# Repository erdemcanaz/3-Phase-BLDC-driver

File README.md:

# 3-Phase-BLDC-driver
A storyline of designing ~400Watt sensored brushless DC motor driver.

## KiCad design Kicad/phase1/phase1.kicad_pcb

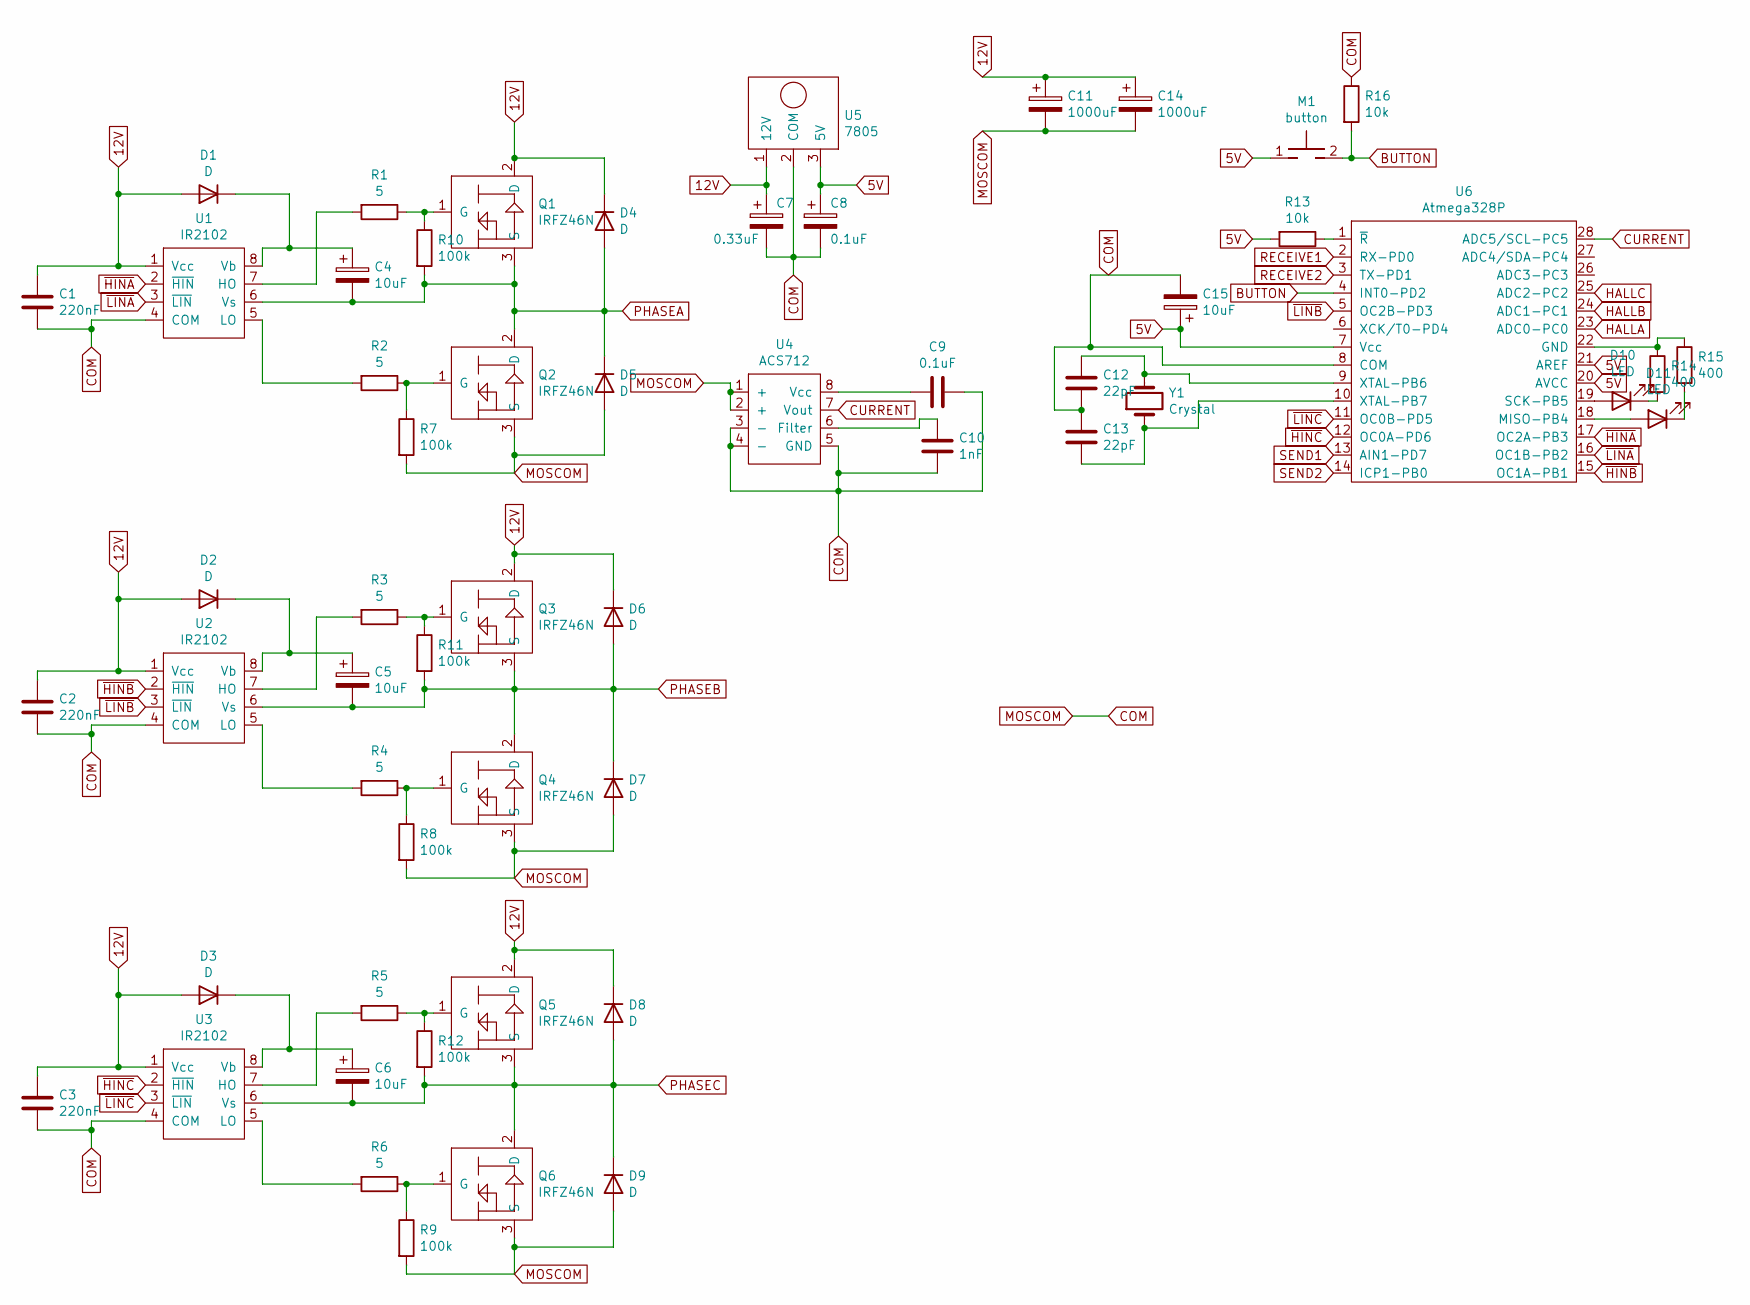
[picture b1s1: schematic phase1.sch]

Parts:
C1, C2, C3: 220nF; 3mm- circle
C4, C5, C6, C15: 10uF; SMD-1210
C7: 0.33uF; 3mm- circle
C8, C9: 0.1uF; 3mm- circle
C10: 1nF; 3mm- circle
C11, C14: 1000uF; 10mm circle
C12, C13: 22pF; 3mm- circle
D1, D2, D3: D; M7
D4, D5, D6, D7, D8, D9: D; SK52-510
D10, D11: LED; LED_D3.0mm
M1: button
Q1, Q2, Q3, Q4, Q5, Q6: IRFZ46N; YATIK-TO222
R1, R2, R3, R4, R5, R6: 5; R_1210_3225Metric
R7, R8, R9, R10, R11, R12: 100k; R_1210_3225Metric
R13: 10k; R_1210_3225Metric
R14, R15: 400; R_1218_3246Metric
R16: 10k; R_1218_3246Metric
U1, U2, U3: IR2102; DIP-8_296_ELL
U4: ACS712; SOIC-8
U5: 7805; YATIK-TO222
U6: Atmega328P; DIP-28_296_ELL
Y1: Crystal; Crystal_HC52-6mm_Vertical

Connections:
5V: C8.1, C15.1, M1.1, R13.2, U5.3 (5V), U6.7 (Vcc), U6.20 (AVCC), U6.21 (AREF)
12V: C1.1, C2.1, C3.1, C7.1, C11.1, C14.1, D1.2 (A), D2.2 (A), D3.2 (A), D4.1 (K), D6.1 (K), D8.1 (K), Q1.2 (D), Q3.2 (D), Q5.2 (D), U1.1 (Vcc), U2.1 (Vcc), U3.1 (Vcc), U5.1 (12V)
BUTTON: M1.2, R16.2, U6.4 (INT0-PD2)
COM: C1.2, C2.2, C3.2, C7.2, C8.2, C9.2, C10.2, C11.2, C12.2, C13.1, C14.2, C15.2, D5.2 (A), D7.2 (A), D9.2 (A), Q2.3 (S), Q4.3 (S), Q6.3 (S), R7.2, R8.2, R9.2, R16.1, U1.4 (COM), U2.4 (COM), U3.4 (COM), U4.1 (+), U4.2 (+), U4.3 (-), U4.4 (-), U4.5 (GND), U5.2 (COM), U6.8 (COM)
CURRENT: U4.7 (Vout), U6.28 (ADC5/SCL-PC5)
HALLA: U6.23 (ADC0-PC0)
HALLB: U6.24 (ADC1-PC1)
HALLC: U6.25 (ADC2-PC2)
unnamed: C4.1, D1.1 (K), U1.8 (Vb)
unnamed: C5.1, D2.1 (K), U2.8 (Vb)
unnamed: C6.1, D3.1 (K), U3.8 (Vb)
unnamed: C9.1, U4.8 (Vcc)
unnamed: C10.1, U4.6 (Filter)
unnamed: C12.1, U6.9 (XTAL-PB6), Y1.2
unnamed: C13.2, U6.10 (XTAL-PB7), Y1.1
unnamed: D10.1 (K), R14.2
unnamed: D10.2 (A), U6.19 (SCK-PB5)
unnamed: D11.1 (K), R15.2
unnamed: D11.2 (A), U6.18 (MISO-PB4)
unnamed: Q1.1 (G), R1.1, R10.1
unnamed: Q2.1 (G), R2.1, R7.1
unnamed: Q3.1 (G), R3.1, R11.1
unnamed: Q4.1 (G), R4.1, R8.1
unnamed: Q5.1 (G), R5.1, R12.1
unnamed: Q6.1 (G), R6.1, R9.1
unnamed: R1.2, U1.7 (HO)
unnamed: R2.2, U1.5 (LO)
unnamed: R3.2, U2.7 (HO)
unnamed: R4.2, U2.5 (LO)
unnamed: R5.2, U3.7 (HO)
unnamed: R6.2, U3.5 (LO)
unnamed: R13.1, U6.1 (~R)
unnamed: R14.1, R15.1, U6.22 (GND)
PHASEA: C4.2, D4.2 (A), D5.1 (K), Q1.3 (S), Q2.2 (D), R10.2, U1.6 (Vs)
PHASEB: C5.2, D6.2 (A), D7.1 (K), Q3.3 (S), Q4.2 (D), R11.2, U2.6 (Vs)
PHASEC: C6.2, D8.2 (A), D9.1 (K), Q5.3 (S), Q6.2 (D), R12.2, U3.6 (Vs)
RECEIVE1: U6.2 (RX-PD0)
RECEIVE2: U6.3 (TX-PD1)
SEND1: U6.13 (AIN1-PD7)
SEND2: U6.14 (ICP1-PB0)
~HINA: U1.2 (~HIN), U6.17 (OC2A-PB3)
~HINB: U2.2 (~HIN), U6.15 (OC1A-PB1)
~HINC: U3.2 (~HIN), U6.12 (OC0A-PD6)
~LINA: U1.3 (~LIN), U6.16 (OC1B-PB2)
~LINB: U2.3 (~LIN), U6.5 (OC2B-PD3)
~LINC: U3.3 (~LIN), U6.11 (OC0B-PD5)

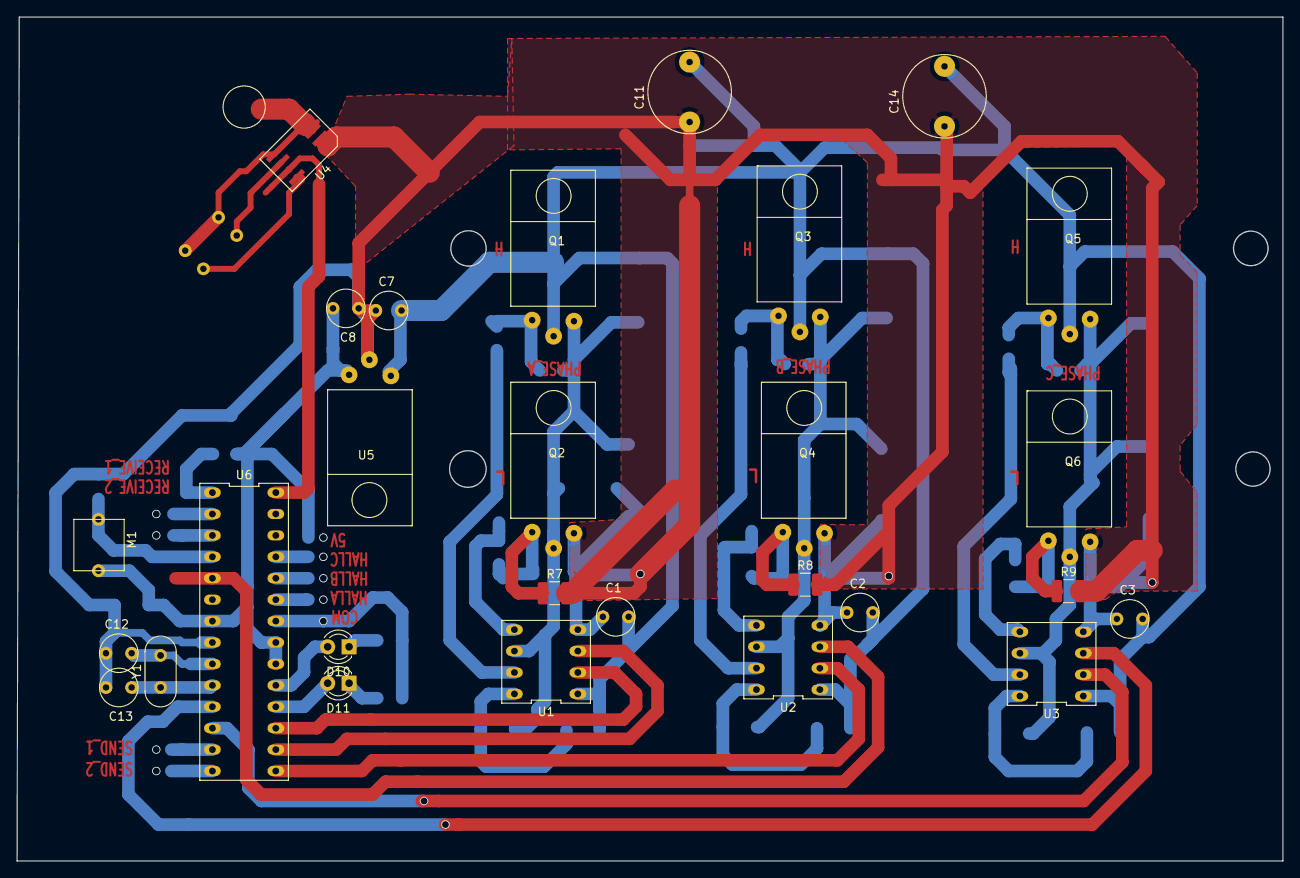
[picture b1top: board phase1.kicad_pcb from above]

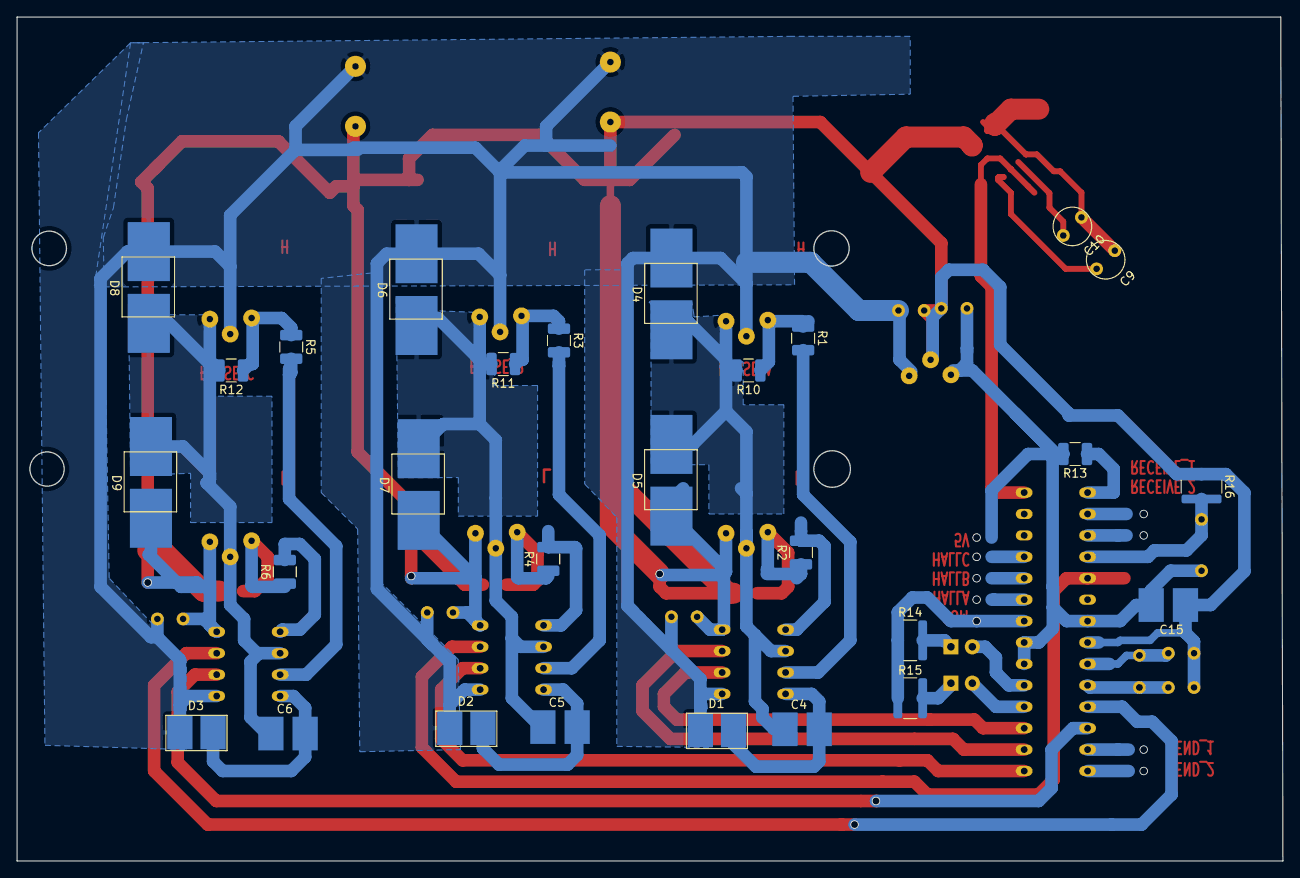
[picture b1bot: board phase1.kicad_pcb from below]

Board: 2 copper layers, 150.0 x 100.0 mm, 56 parts (28 on the bottom side), 39 nets.

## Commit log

2020-10-20 PWM register testing
    Trying to achive 20-30Khz hardware controlled PWM signal
2020-12-04 .
    .
